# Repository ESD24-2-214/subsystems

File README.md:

# Subsystems
This is a repo for different subsystems in the project.
:D

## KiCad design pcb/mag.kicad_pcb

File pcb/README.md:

# Redesign
1. All of the LDR's should be facing the same direction.
2. I2C should be routed on the bottom.
3. The decoupling capacitor for the H brigth should have the corrent footprint
4. The GY-91 should have mounting holes
5. positive negative name in the copper
6. all text should be on a custom layer
7. new microcontroller

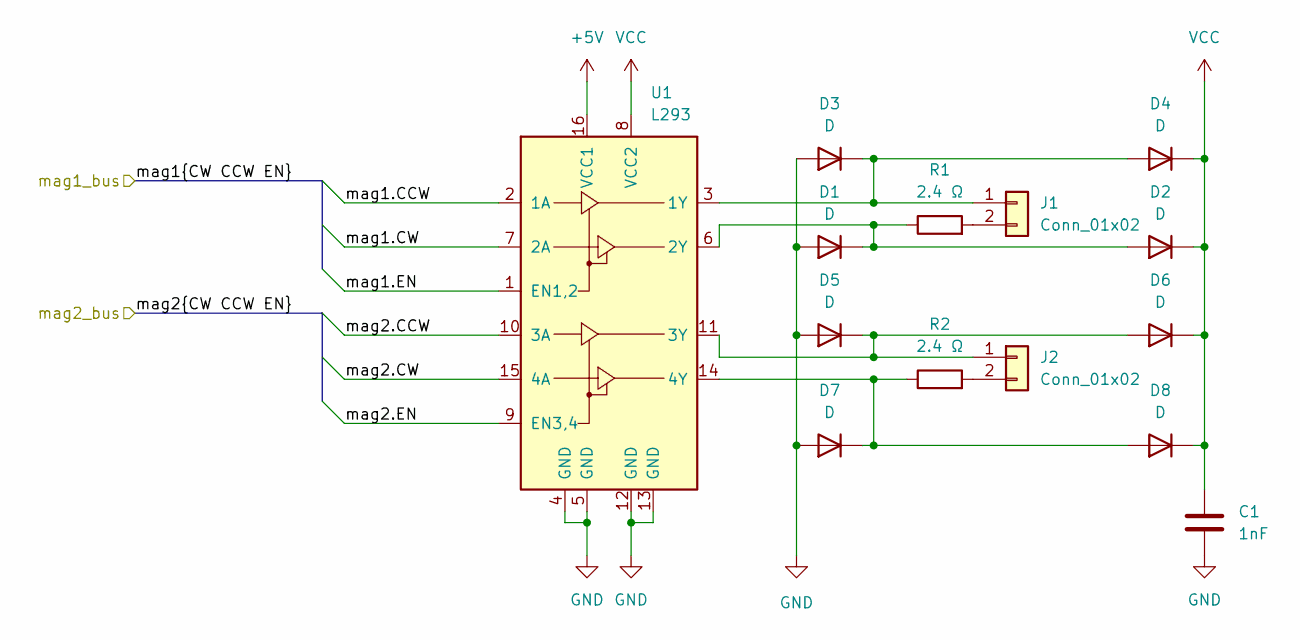
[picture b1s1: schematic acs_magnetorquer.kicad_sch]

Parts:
C1: 1nF; C_Disc_D3.4mm_W2.1mm_P2.50mm
D1, D2, D3, D4, D5, D6, D7, D8: D; D_A-405_P7.62mm_Horizontal
J1, J2: Conn_01x02; SolderWire-0.1sqmm_1x02_P3.6mm_D0.4mm_OD1mm
R1, R2: 2.4 Ω; R_Axial_DIN0309_L9.0mm_D3.2mm_P12.70mm_Horizontal
U1: L293; DIP-16_W7.62mm

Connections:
+5V: U1.16 (VCC1); also elsewhere on the board
/ACS_mag/mag1.CCW: U1.2 (1A); also elsewhere on the board
/ACS_mag/mag1.CW: U1.7 (2A); also elsewhere on the board
/ACS_mag/mag1.EN: U1.1 (EN1,2); also elsewhere on the board
/ACS_mag/mag2.CCW: U1.10 (3A); also elsewhere on the board
/ACS_mag/mag2.CW: U1.15 (4A); also elsewhere on the board
/ACS_mag/mag2.EN: U1.9 (EN3,4); also elsewhere on the board
GND: C1.2, D1.2 (A), D3.2 (A), D5.2 (A), D7.2 (A), U1.4 (GND), U1.5 (GND), U1.12 (GND), U1.13 (GND); also elsewhere on the board
unnamed: D1.1 (K), D2.2 (A), R1.1, U1.6 (2Y)
unnamed: D3.1 (K), D4.2 (A), J1.1, U1.3 (1Y)
unnamed: D5.1 (K), D6.2 (A), J2.1, U1.11 (3Y)
unnamed: D7.1 (K), D8.2 (A), R2.1, U1.14 (4Y)
unnamed: J1.2, R1.2
unnamed: J2.2, R2.2
VCC: C1.1, D2.1 (K), D4.1 (K), D6.1 (K), D8.1 (K), U1.8 (VCC2); also elsewhere on the board

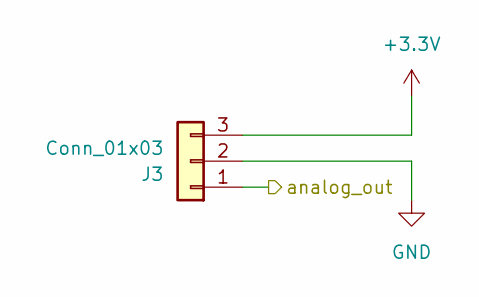
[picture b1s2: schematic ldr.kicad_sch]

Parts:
J3: Conn_01x03; PinHeader_1x03_P2.54mm_Vertical

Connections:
+3.3V: J3.3; also elsewhere on the board
/LDR.Forward: J3.1; also elsewhere on the board
GND: J3.2; also elsewhere on the board

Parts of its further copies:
J4, J5, J6: Conn_01x03; PinHeader_1x03_P2.54mm_Vertical

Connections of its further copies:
+3.3V: J4.3, J5.3, J6.3; also elsewhere on the board
/LDR.Back: J4.1; also elsewhere on the board
/LDR.Left: J5.1; also elsewhere on the board
/LDR.Right: J6.1; also elsewhere on the board
GND: J4.2, J5.2, J6.2; also elsewhere on the board

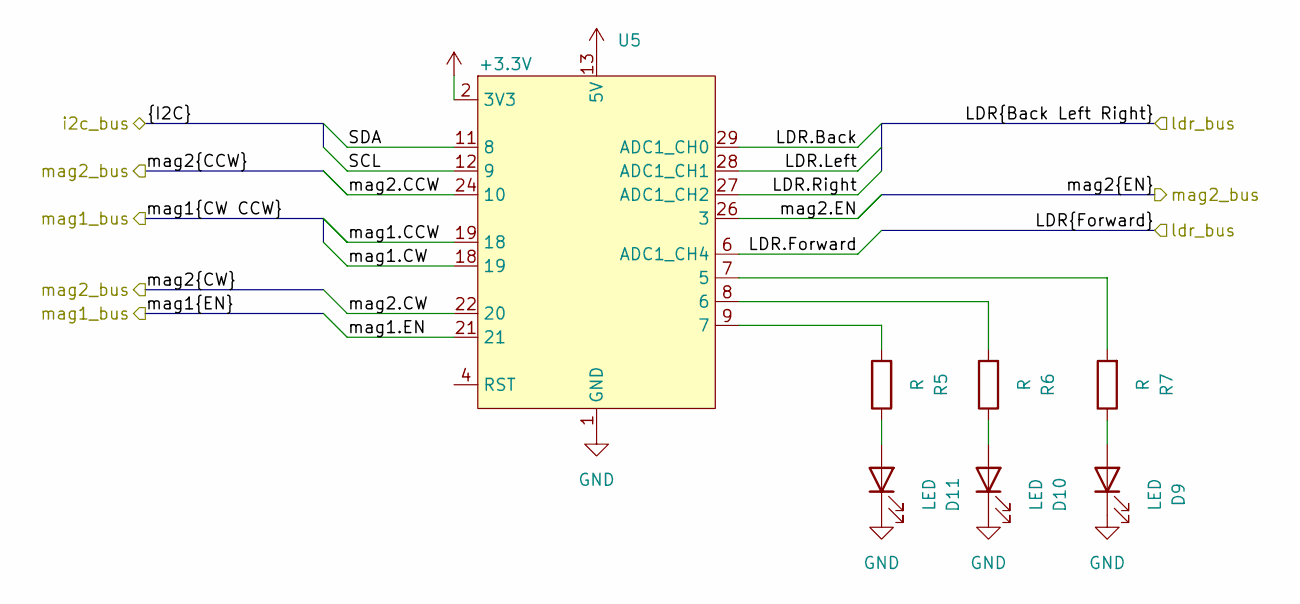
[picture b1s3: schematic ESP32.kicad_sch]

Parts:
D9, D10, D11: LED; LED_D5.0mm
R5, R6, R7: R; R_Axial_DIN0207_L6.3mm_D2.5mm_P7.62mm_Horizontal
U5: ESP32-C3-DevKitM-1

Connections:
+3.3V: U5.2 (3V3), U5.3 (3V3); also elsewhere on the board
+5V: U5.13 (5V), U5.14 (5V); also elsewhere on the board
/ACS_mag/mag1.CCW: U5.19 (18); also elsewhere on the board
/ACS_mag/mag1.CW: U5.18 (19); also elsewhere on the board
/ACS_mag/mag1.EN: U5.21; also elsewhere on the board
/ACS_mag/mag2.CCW: U5.24 (10); also elsewhere on the board
/ACS_mag/mag2.CW: U5.22 (20); also elsewhere on the board
/ACS_mag/mag2.EN: U5.26 (3); also elsewhere on the board
/ESP32/SCL: U5.12 (9); also elsewhere on the board
/ESP32/SDA: U5.11 (8); also elsewhere on the board
/LDR.Back: U5.29 (ADC1_CH0); also elsewhere on the board
/LDR.Forward: U5.6 (ADC1_CH4); also elsewhere on the board
/LDR.Left: U5.28 (ADC1_CH1); also elsewhere on the board
/LDR.Right: U5.27 (ADC1_CH2); also elsewhere on the board
GND: D9.1 (K), D10.1 (K), D11.1 (K), U5.1 (GND), U5.5 (GND), U5.10 (GND), U5.15 (GND), U5.16 (GND), U5.17 (GND), U5.20 (GND), U5.23 (GND), U5.25 (GND), U5.30 (GND); also elsewhere on the board
unnamed: D9.2 (A), R7.1
unnamed: D10.2 (A), R6.1
unnamed: D11.2 (A), R5.1
unnamed: R7.2, U5.7 (5)
unnamed: R6.2, U5.8 (6)
unnamed: R5.2, U5.9 (7)

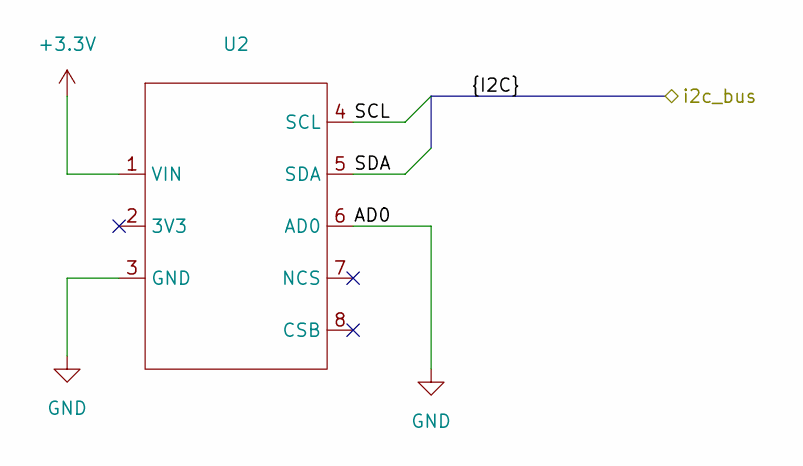
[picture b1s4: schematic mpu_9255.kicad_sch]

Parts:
U2: GY-91

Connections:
+3.3V: U2.1 (VIN); also elsewhere on the board
/ESP32/SCL: U2.4 (SCL); also elsewhere on the board
/ESP32/SDA: U2.5 (SDA); also elsewhere on the board
GND: U2.3 (GND), U2.6 (AD0); also elsewhere on the board

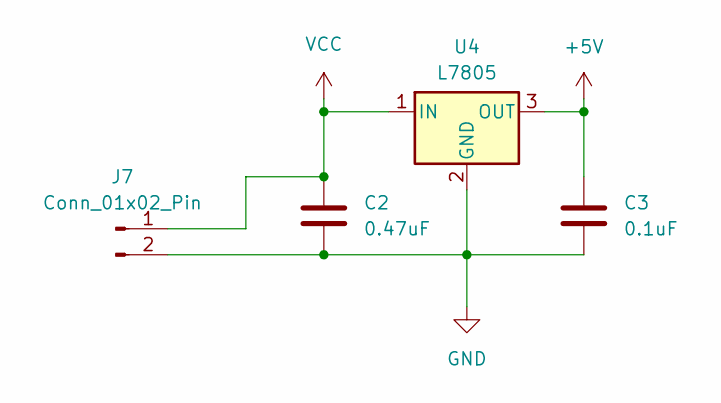
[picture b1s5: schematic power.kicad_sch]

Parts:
C2: 0.47uF; C_Rect_L7.0mm_W4.5mm_P5.00mm
C3: 0.1uF; C_Rect_L7.0mm_W2.0mm_P5.00mm
J7: Conn_01x02_Pin; TerminalBlock_MaiXu_MX126-5.0-02P_1x02_P5.00mm
U4: L7805; TO-220-3_Horizontal_TabDown

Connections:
+5V: C3.1, U4.3 (OUT); also elsewhere on the board
GND: C2.2, C3.2, J7.2, U4.2 (GND); also elsewhere on the board
VCC: C2.1, J7.1, U4.1 (IN); also elsewhere on the board

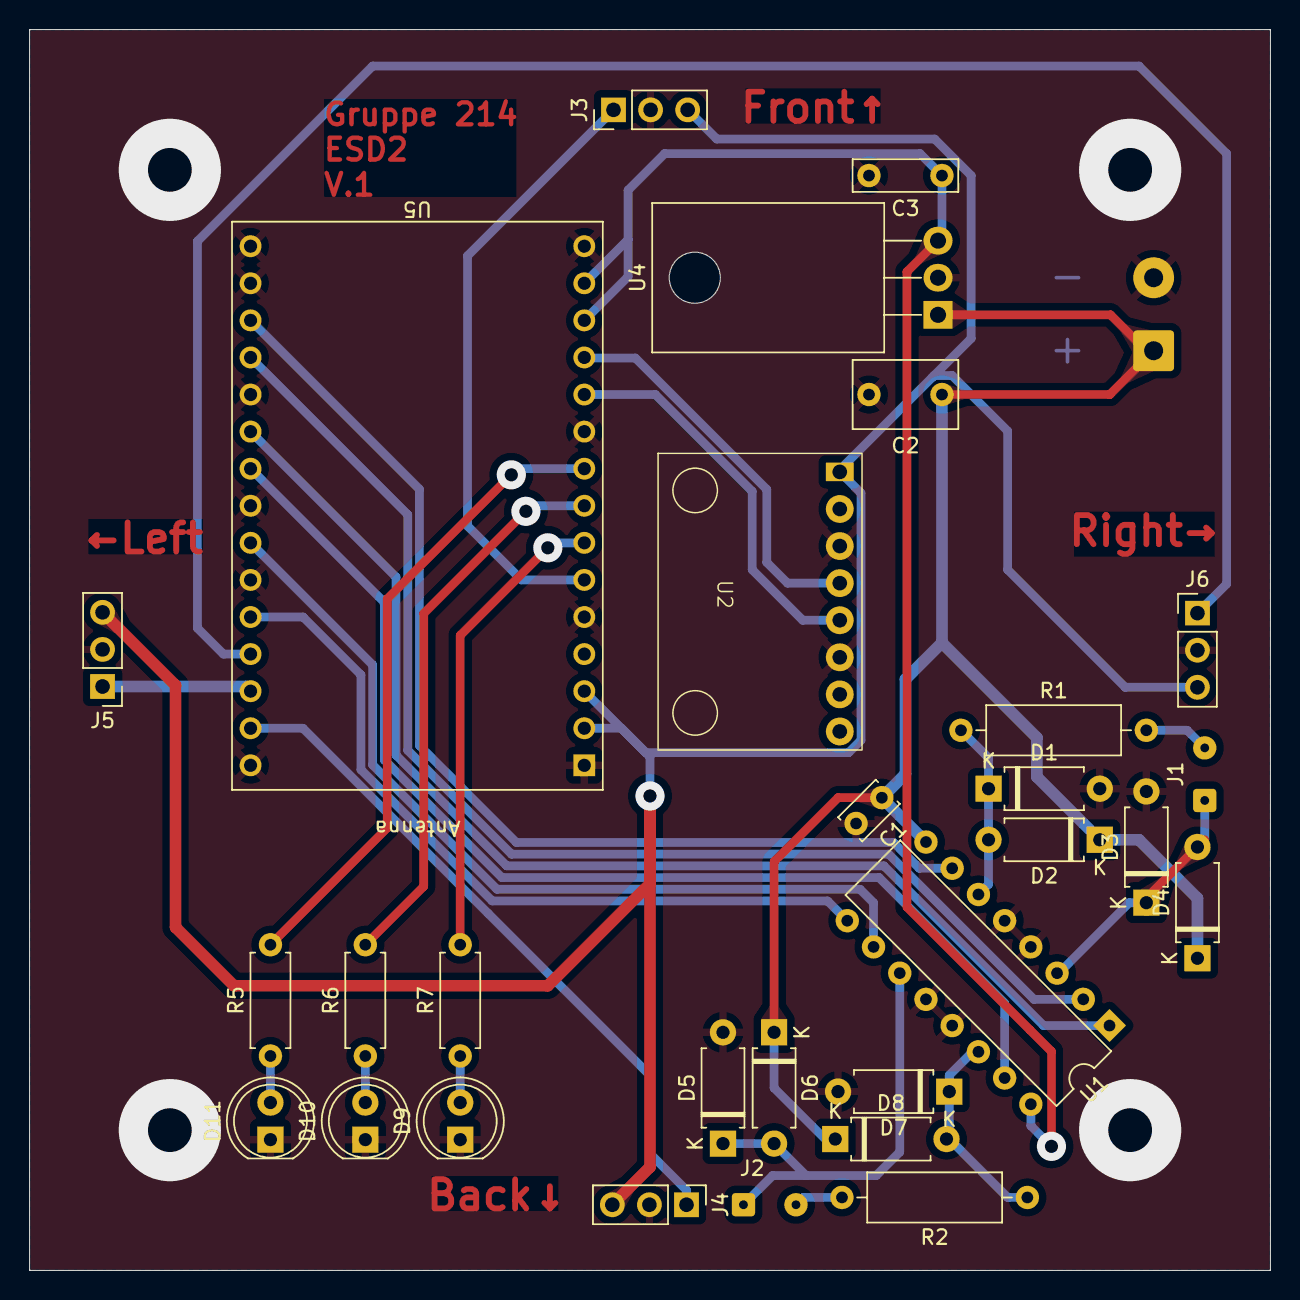
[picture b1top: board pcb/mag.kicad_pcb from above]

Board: 2 copper layers, 85.0 x 85.0 mm, 30 parts (1 on the bottom side), 28 nets.

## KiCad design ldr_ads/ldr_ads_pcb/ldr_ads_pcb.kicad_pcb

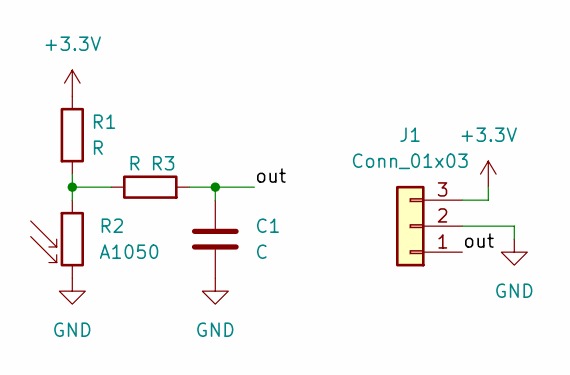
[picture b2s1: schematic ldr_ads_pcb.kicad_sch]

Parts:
C1: C; C_Rect_L7.2mm_W3.5mm_P5.00mm_FKS2_FKP2_MKS2_MKP2
J1: Conn_01x03; PinHeader_1x03_P2.54mm_Horizontal
R1, R3: R; R_Axial_DIN0207_L6.3mm_D2.5mm_P10.16mm_Horizontal
R2: A1050; R_LDR_D6.4mm_P3.4mm_Vertical

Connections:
+3.3V: J1.3, R1.1
/out: C1.1, J1.1, R3.2
GND: C1.2, J1.2, R2.2
unnamed: R1.2, R2.1, R3.1

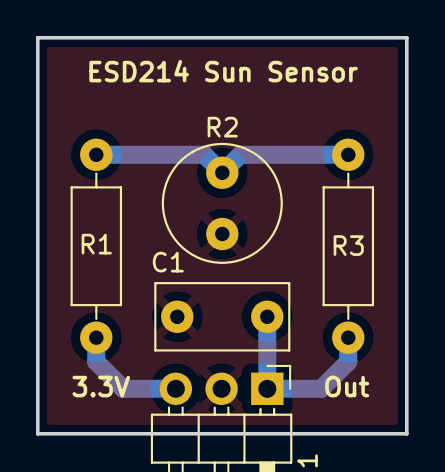
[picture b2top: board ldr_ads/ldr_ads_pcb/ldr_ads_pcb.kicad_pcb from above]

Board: 2 copper layers, 20.5 x 22.0 mm, 5 parts (0 on the bottom side), 4 nets.

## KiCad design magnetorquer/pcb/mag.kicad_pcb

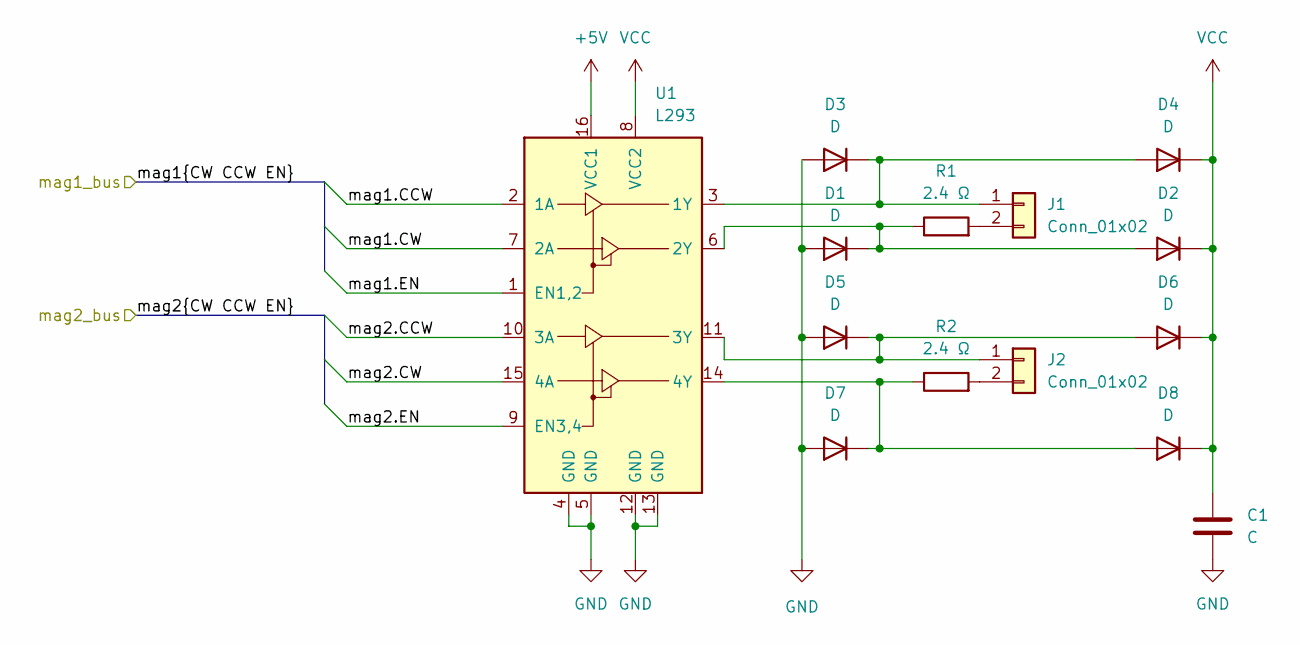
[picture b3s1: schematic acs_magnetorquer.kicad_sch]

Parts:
C1: C; C_Radial_D4.0mm_H5.0mm_P1.50mm
D1, D2, D3, D4, D5, D6, D7, D8: D; D_A-405_P7.62mm_Horizontal
J1, J2: Conn_01x02; SolderWire-0.1sqmm_1x02_P3.6mm_D0.4mm_OD1mm
R1, R2: 2.4 Ω; R_Axial_DIN0309_L9.0mm_D3.2mm_P12.70mm_Horizontal
U1: L293; DIP-16_W7.62mm

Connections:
+5V: U1.16 (VCC1); also elsewhere on the board
/ACS_mag/mag1.CCW: U1.2 (1A); also elsewhere on the board
/ACS_mag/mag1.CW: U1.7 (2A); also elsewhere on the board
/ACS_mag/mag1.EN: U1.1 (EN1,2); also elsewhere on the board
/ACS_mag/mag2.CCW: U1.10 (3A); also elsewhere on the board
/ACS_mag/mag2.CW: U1.15 (4A); also elsewhere on the board
/ACS_mag/mag2.EN: U1.9 (EN3,4); also elsewhere on the board
unnamed: D1.1 (K), D2.2 (A), R1.1, U1.6 (2Y)
unnamed: D3.1 (K), D4.2 (A), J1.1, U1.3 (1Y)
unnamed: D5.1 (K), D6.2 (A), J2.1, U1.11 (3Y)
unnamed: D7.1 (K), D8.2 (A), R2.1, U1.14 (4Y)
unnamed: J1.2, R1.2
unnamed: J2.2, R2.2
VCC: C1.1, D2.1 (K), D4.1 (K), D6.1 (K), D8.1 (K), U1.8 (VCC2); also elsewhere on the board

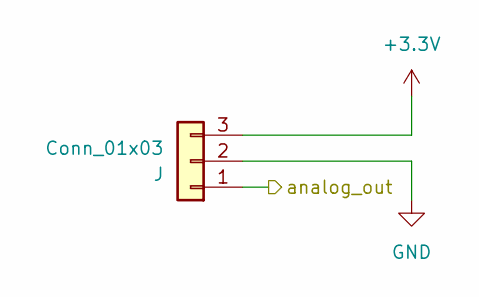
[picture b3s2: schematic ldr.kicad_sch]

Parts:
J: Conn_01x03; PinHeader_1x03_P2.54mm_Vertical

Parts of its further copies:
J4, J5, J6: Conn_01x03; PinHeader_1x03_P2.54mm_Vertical

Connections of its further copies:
+3.3V: J4.3, J5.3, J6.3; also elsewhere on the board
/LDR.Back: J4.1; also elsewhere on the board
/LDR.Left: J5.1; also elsewhere on the board
/LDR.Right: J6.1; also elsewhere on the board

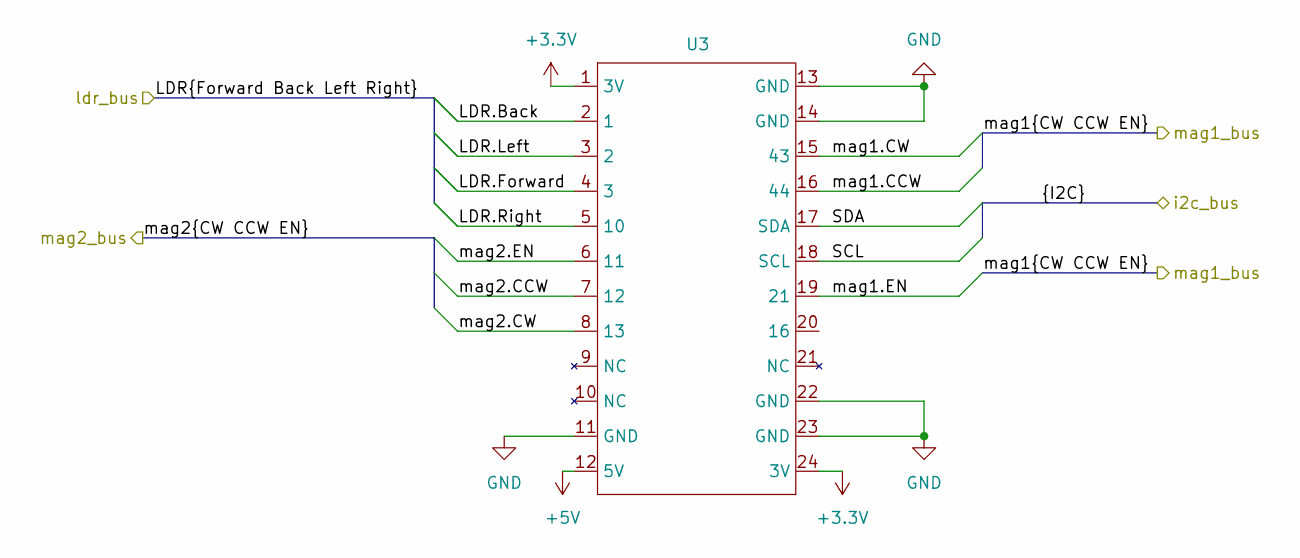
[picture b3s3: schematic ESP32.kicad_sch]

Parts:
U3: LILYGO_T-Display_ESP32-S3

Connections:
+3.3V: U3.1 (3V), U3.24 (3V); also elsewhere on the board
+5V: U3.12 (5V); also elsewhere on the board
/ACS_mag/mag1.CCW: U3.16 (44); also elsewhere on the board
/ACS_mag/mag1.CW: U3.15 (43); also elsewhere on the board
/ACS_mag/mag1.EN: U3.19 (21); also elsewhere on the board
/ACS_mag/mag2.CCW: U3.7 (12); also elsewhere on the board
/ACS_mag/mag2.CW: U3.8 (13); also elsewhere on the board
/ACS_mag/mag2.EN: U3.6 (11); also elsewhere on the board
/ESP32/SCL: U3.18 (SCL); also elsewhere on the board
/ESP32/SDA: U3.17 (SDA); also elsewhere on the board
/LDR.Back: U3.2 (1); also elsewhere on the board
/LDR.Forward: U3.4 (3); also elsewhere on the board
/LDR.Left: U3.3 (2); also elsewhere on the board
/LDR.Right: U3.5 (10); also elsewhere on the board

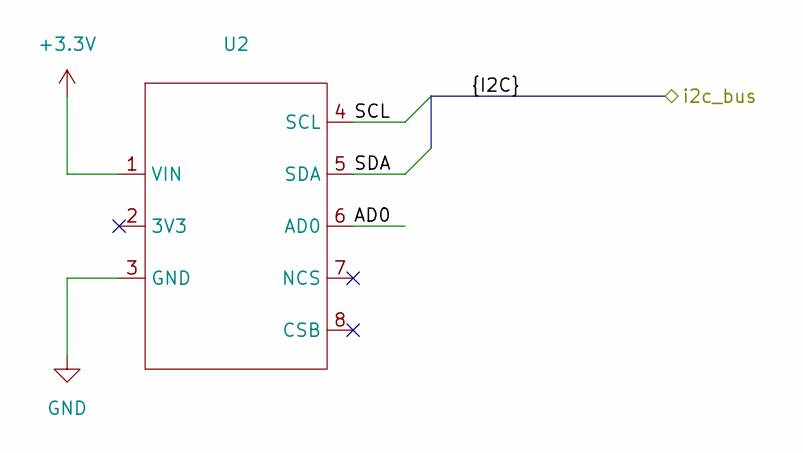
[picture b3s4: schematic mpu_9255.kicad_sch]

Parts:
U2: GY-91

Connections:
+3.3V: U2.1 (VIN); also elsewhere on the board
/ESP32/SCL: U2.4 (SCL); also elsewhere on the board
/ESP32/SDA: U2.5 (SDA); also elsewhere on the board

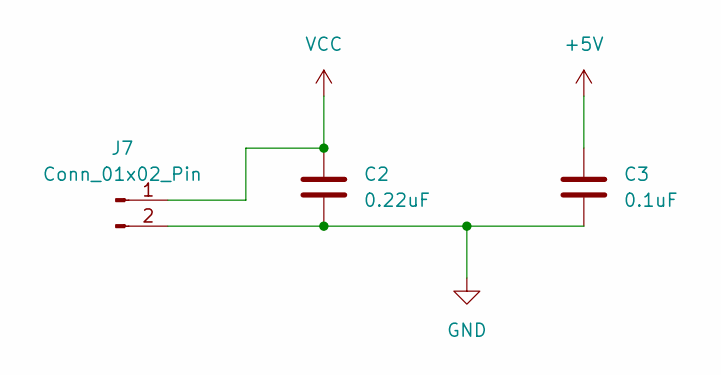
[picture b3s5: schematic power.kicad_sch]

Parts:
C2: 0.22uF; C_Rect_L7.0mm_W2.5mm_P5.00mm
C3: 0.1uF; C_Rect_L7.0mm_W2.5mm_P5.00mm
J7: Conn_01x02_Pin; PinHeader_1x02_P2.54mm_Vertical

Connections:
+5V: C3.1; also elsewhere on the board
VCC: C2.1, J7.1; also elsewhere on the board

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
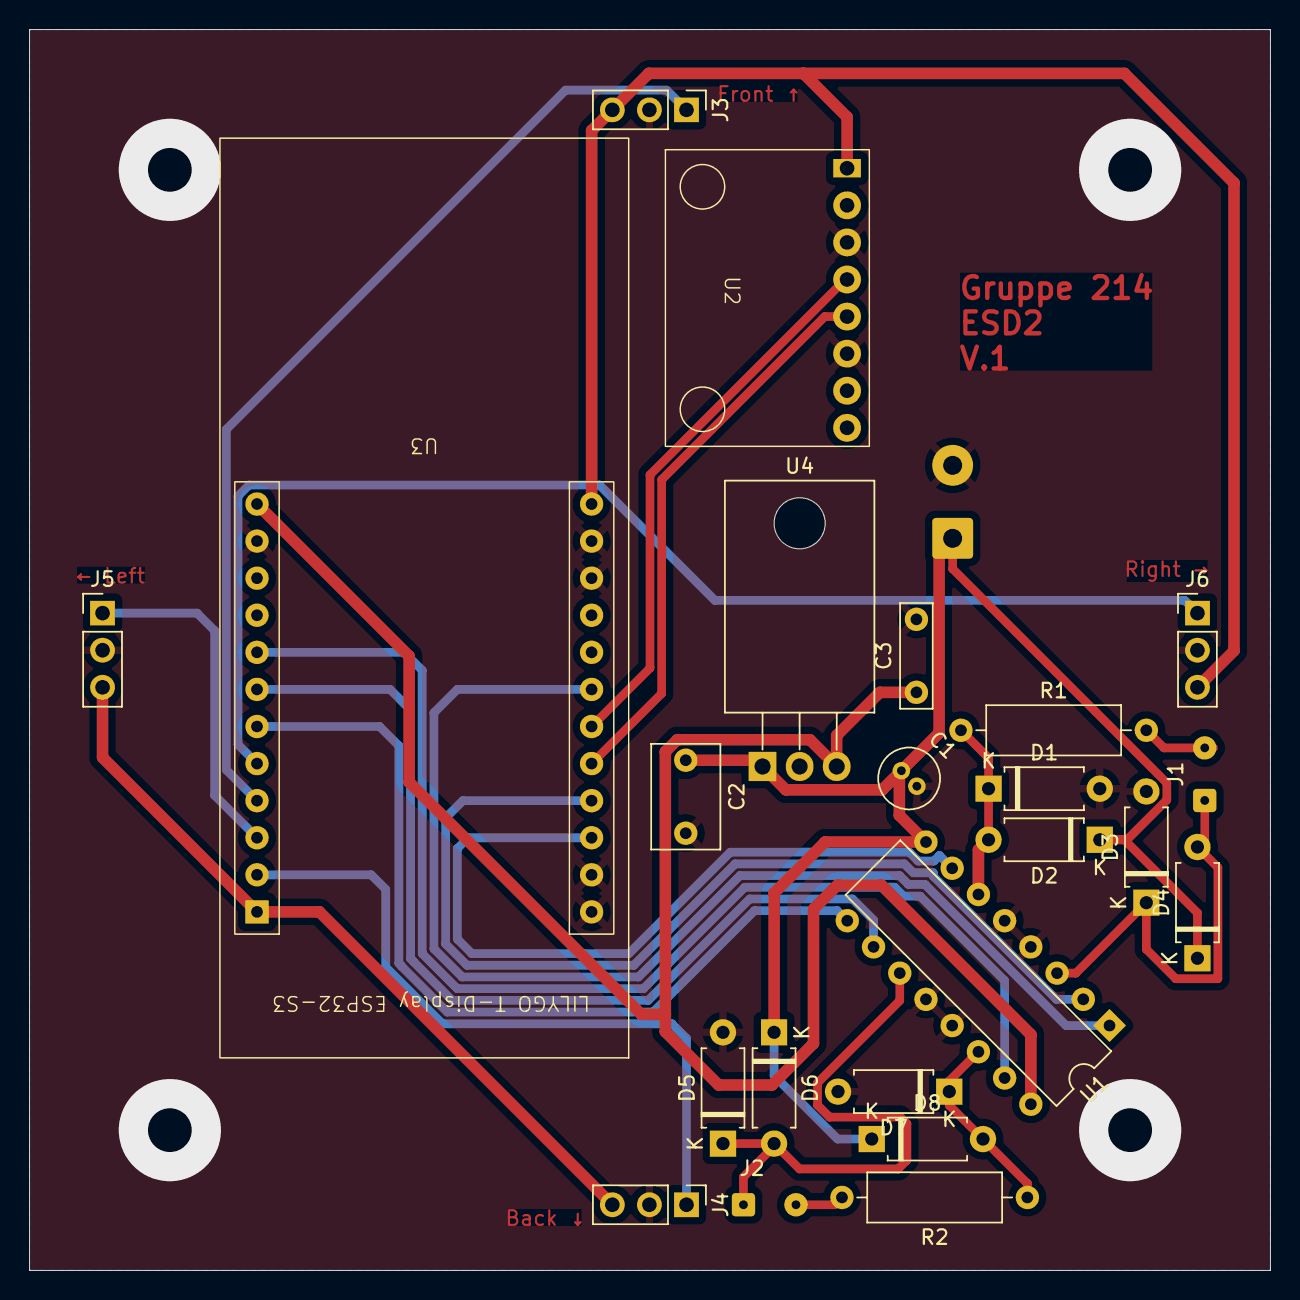
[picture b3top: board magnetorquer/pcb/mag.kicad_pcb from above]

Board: 2 copper layers, 85.0 x 85.0 mm, 24 parts (1 on the bottom side), 22 nets.

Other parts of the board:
J3: Conn_01x03; PinHeader_1x03_P2.54mm_Vertical
U4: L7805; TO-220-3_Horizontal_TabDown

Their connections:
+3.3V: J3.3; also elsewhere on the board
+5V: U4.3 (OUT); also elsewhere on the board
/LDR.Forward: J3.1; also elsewhere on the board
VCC: U4.1 (IN); also elsewhere on the board

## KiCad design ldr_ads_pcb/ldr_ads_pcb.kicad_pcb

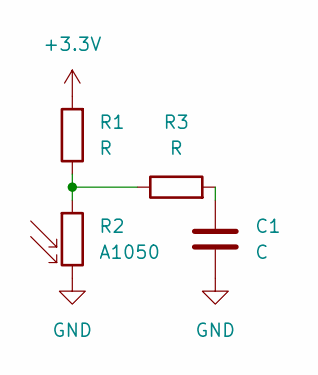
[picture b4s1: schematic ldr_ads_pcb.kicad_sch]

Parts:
C1: C; C_Rect_L4.6mm_W2.0mm_P2.50mm_MKS02_FKP02
R1, R3: R; R_Axial_DIN0414_L11.9mm_D4.5mm_P15.24mm_Horizontal
R2: A1050; R_LDR_D6.4mm_P3.4mm_Vertical

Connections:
+3.3V: R1.2
GND: C1.2, R2.2
unnamed: C1.1, R3.2
unnamed: R1.1, R2.1, R3.1

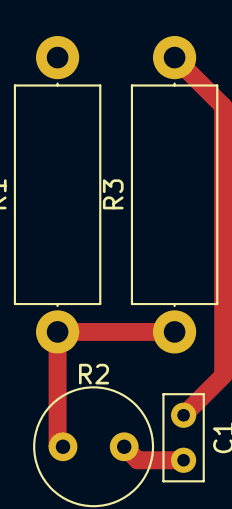
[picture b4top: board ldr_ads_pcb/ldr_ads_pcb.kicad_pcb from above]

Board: 2 copper layers, 4 parts (0 on the bottom side), 3 nets.

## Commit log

2025-03-10 init: ldr ads, platformio, esp32
2025-03-10 init: The rest
2025-03-10 fix: actual title
2025-03-11 feat: add ldr pcb daughterboard
2025-03-11 LTspice diagram og Maple udregninger
2025-03-13 feat: ready pcb
2025-03-14 init: add openscad magnetorquer model
2025-03-17 "statup"
2025-03-17 .gitnore
2025-03-17 magnotometer on off funktion
2025-03-18 init: add readme
2025-03-18 feat: add magnetorquer math
2025-03-18 feat: add magnetorquer git repo
2025-03-18 init: hbridge
2025-03-20 read- and configfunction
2025-03-20 untested read function made
2025-03-20 untested++
2025-03-21 fix: change value afte prototype
2025-03-21 Test kode til H bridge
2025-03-21 seemingly working code. comments are yet to be made
2025-03-21 comments
2025-03-31 feat: add start of control loop sym
    fn that are done:
    angle_bivector_err
    pid
    actuator
2025-04-01 feat: add angle_from_torque, rotate_vector, test
    It is tested up ageints ga_lib_rust
2025-04-10 new changes stil bugs...
2025-04-10 same
2025-04-13 the beginnig of a master i2c lib
2025-04-15 fix: tested sym. got pid val
2025-04-15 feat: ref, rotation formula for vec & bivec
    Implement rotation formula for vector and bivector
    with the use of rotors.
2025-04-16 untested i2c lib
2025-04-16 fix: torque to rot angle
    I had used angluar-acc instead of angluar-velocity
2025-04-19 fix: better plot more math func
2025-04-19 fix: change ref frame with change of basis
    Rotations only work when one of the basis are in the same direction.
    This is not always the case.
2025-04-21 feat: interopt between ref frame & control loop
2025-04-22 feat: add hardware schematic
    multi file kicad project
2025-04-22 add lilygo pinout image
2025-04-22 Tilføjet ":D" til readme, fordi.
2025-04-22 It's taking form
2025-04-24 Kicad Schematic til ESP32 lilygo t-display s3
2025-04-24 feat: add picture with size of gy-91
2025-04-24 fix: changed basis to orthonormal
2025-04-24 fix: remove produced pdf
2025-04-24 Alt det der manglede til Kicad
2025-04-24 feat: lilygo s3 sch/footprint clean up sch
2025-04-24 feat: upload all changes for sch
2025-04-24 new functions added, untestet but almost done, i hope...
2025-04-25 it works bud don't seme to be calibrated
2025-04-25 start routing pcb
    It needs a power regulator and a battery terminal
2025-04-28 Data reading worksgit status
2025-04-28 Quick edit
2025-04-28 Power reg. and v.1 print
2025-04-29 Added env for ESP32-C3-dev
2025-04-29 Step respons for LDR
2025-04-29 fix: change mcu, add led
2025-05-01 fix: move control loop fn to sep file in r_c
2025-05-01 feat: init in the final mcu code
2025-05-01 feat: block diagram of the full code
2025-05-05 pcb change and ldr setp csv file add
2025-05-05 changed Vector struct to e1,e2,e3
2025-05-05 renamed mpu_i2c to data_task
2025-05-05 created LDR lib
2025-05-05 changes to LDR data_task
2025-05-05 added my FreeRTOS test
2025-05-06 read and init LDR
2025-05-06 FreeRTOS test. Queues and tasks
2025-05-06 LDR lib added, not testet
2025-05-06 Not testet
2025-05-07 feat: insert control loop into task in system
2025-05-07 Task created. SensorRead
2025-05-07 Implemented some of sensor read task
2025-05-07 moved const int core to Config.h and fixed main error
2025-05-07 feat: created sensor, scalar queues
2025-05-07 sun_data_read function added
2025-05-07 added sun_read_data
2025-05-07 added .gitignore to ldr_ads
2025-05-07 changed .gitignore
2025-05-07 changed SensorRead
2025-05-07 feat: write scalar to queue
2025-05-07 fixed error
2025-05-07 feat: add nix stuff to FreeRTOS_Test
2025-05-07 feat: add \out to gitignore for pcb
2025-05-07 Hey you
2025-05-07 Hey you stop it
2025-05-07 pin nr
2025-05-07 changed pinnames
2025-05-07 fix: ldr name fix + mutex funtions
2025-05-07 fix it
2025-05-07 fix: ref and current vec using mutex
2025-05-07 Added HBrigde lib and actuator control task
2025-05-07 fix: add msec to log
2025-05-08 Added Serial mutex
2025-05-08 changed DEBUG Macro to ERROR_LOG and PRINT_DEBUG
2025-05-08 fix: test for zero vector in sensor
2025-05-08 added I2C scanning to detect specific addesses
2025-05-08 changed ldr pcb
2025-05-08 changed schematic
2025-05-12 last inderation of ldr_sensor
2025-05-12 added include for stdio.h to fix an error but PRINTF func stil a prob
2025-05-12 changed xQueueResive to xQueuePeek, and added gyro, accl data to data struct
2025-05-12 added a take on a calibation function
2025-05-12 fix: set analog write freq
2025-05-12 fix: chang so more light gives bigger value
2025-05-12 fix: move const to config.hpp: control loop, ldr
2025-05-14 changed read_magnetometer
2025-05-14 added stuf
2025-05-15 Added test_n_debug dir
2025-05-15 added delay to sensor loop
2025-05-15 testing
2025-05-16 added som digital writes but out commented them, and added a way to turn Serial on and of
2025-05-16 hbro test in LTspice
2025-05-19 added freq to 10kHz 50% duty
2025-05-19 fix: add test to sunsensor
2025-05-19 fix: add ldr calicrtion offset bases on test
2025-05-20 fix: tuned the pid controller to fix the kraken
    There is a big problem in the code.
    In speciffic senarios the controller will send the satelitte to e1
    instead of reference.
    I do not know why.
2025-05-21 feat: small pwm example
2025-05-21 Added hardiron bias to magnetometer.
2025-05-21 fix: pwd res down, freq up, pwm test
2025-05-21 feat: pwm test all 4 pins
2025-05-22 lots of stuff changed to ldr and hbro
2025-05-22 un-uncommentet env:debug
2025-05-22 tried to speed up the magnetometre read time
2025-05-22 changed code_block_diagram
2025-05-23 Added magnetometer code and mag.csv, which is mag data. Changed hardware diagram
2025-05-23 semantic changes
2025-05-23 added mag calibation
2025-05-23 fixed scalers yay
2025-05-23 changed values in config
2025-05-23 Added test csv for magnetometer
2025-05-24 found mistake were enable_mag were uncommeted
2025-05-25 changed for testing
2025-05-25 changed LDR_CALIBRATION for debug and added to DEBUG_CONROL for SensorRead, there is a problem with mag determination
